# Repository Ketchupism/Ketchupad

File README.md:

# Ketchupad

A macropad with 4x3 11 switches, 1 rotary switch encoder
- This macropad will be frequently used paired with my macbook so I can use shortcuts in Fusion360, Kicad, opening tabs in chrome, and other software apps / tools
- The rotary Encoder is used for changing the LED's RGB colors
- The bottom case has a 15 degree tilt forward for visuals and less wrist movement
- Black, Red, and White are colors used in this design
- The 3D print includes the knob, top case, and bottom case. 

Challenges
- The worst part of this work was the firmware. The tutorial was hard to follow and a portion of making the QMK was vibecoded
- Making the case also took long because I added many details to be more unqiue and less boxy 

Features
- 11 keys with LED
- Rotary Encoder
- Custom knob for rotary encoder
- Custom case for PCB
- Angled macropad

Tools / Softwares / Resources
resources that are necessary to make this hackpad
- KiCad
- GrabCad
- Hack Club
- Fusion360
- 3D Printer 
- Soldering machine 

BOM
resources that are necessary to make this hackpad
- 1x PCB
- 1x Seeed XIAO RP2040 Microcontroller
- 11x Cherry MX Switches
- 1x EC11 Encoder with switch
- 11x white blank DSA keycaps
- 1x 3D printed case
- 11x through-hole 1N4148 diodes
- 11x SK6812 MINI-E LEDs
- 4x M3x16mm screws
- 4x M3x5mx4mm heatset inserts

Schematic Model

PCB Model

3D Viewing PCB Model

CAD Case Model + PCB Model 

Extra
- This macropad was inspired and funded by the Hack Club Hackpad Program
- This took way too long
- Currently, this project inspired me to move on to creating an entire custom keyboard, with repository https://github.com/Ketchupism/ketchboard , or in my profile to check out the progress i've done.

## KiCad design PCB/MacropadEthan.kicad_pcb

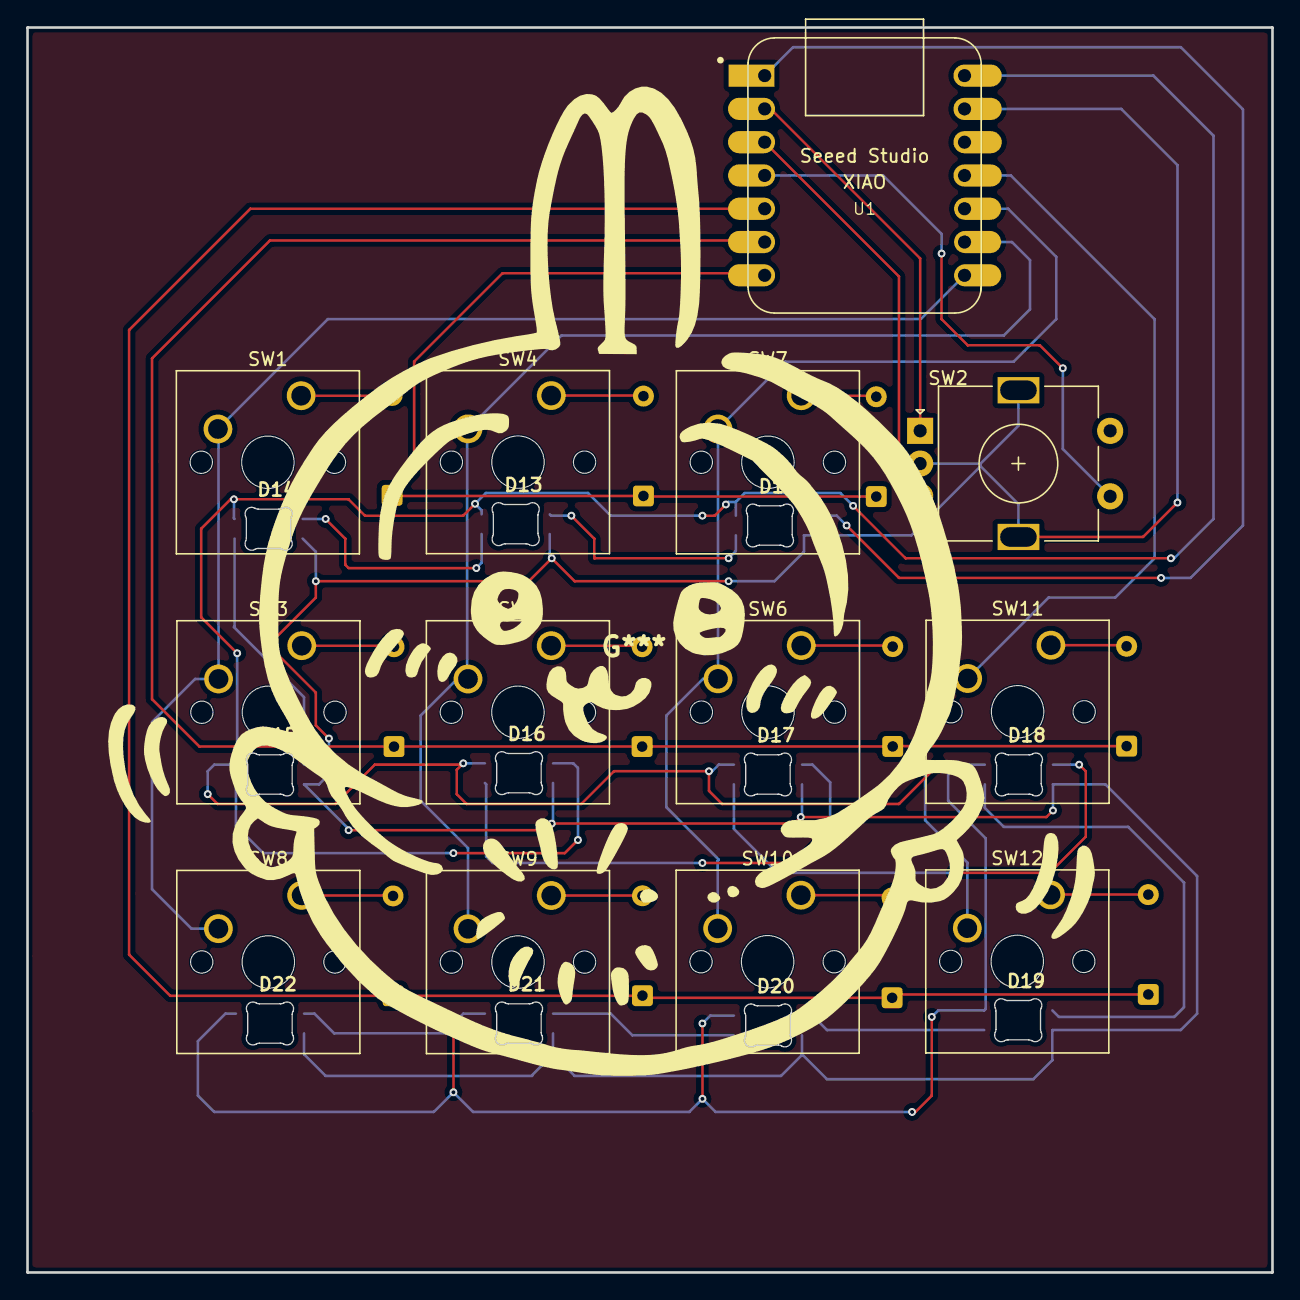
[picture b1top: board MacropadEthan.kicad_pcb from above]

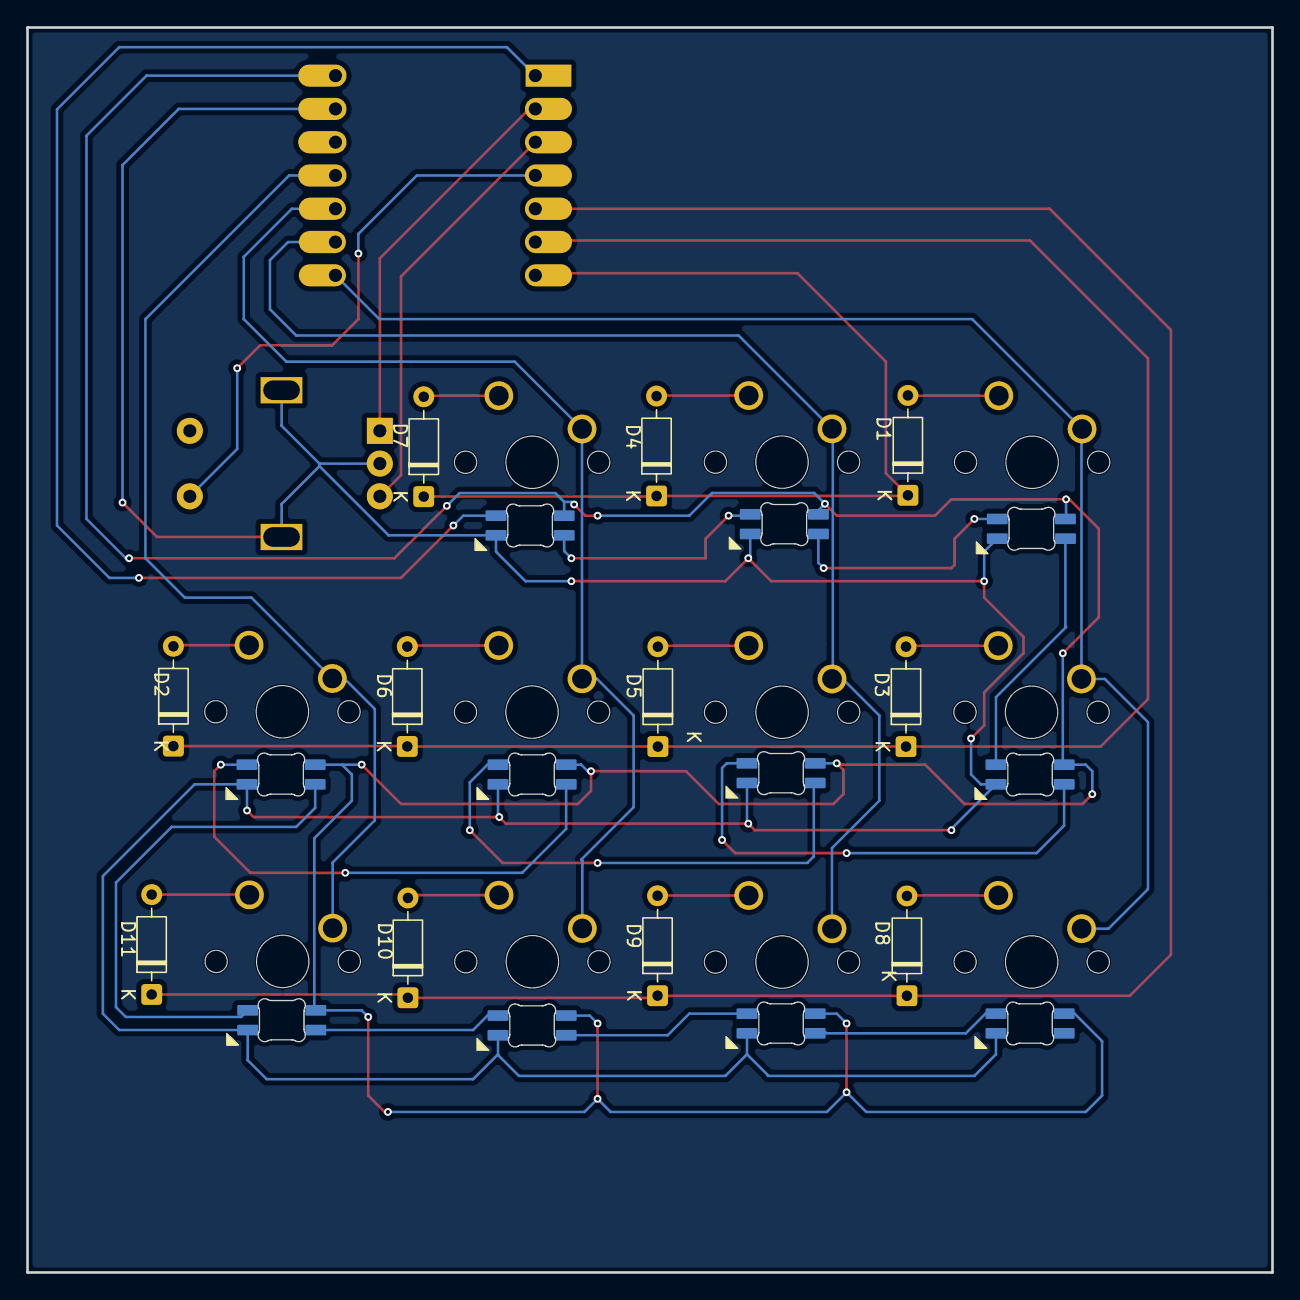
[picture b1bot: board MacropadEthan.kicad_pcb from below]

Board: 2 copper layers, 95.0 x 95.0 mm, 35 parts (11 on the bottom side), 34 nets.

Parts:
D1, D2, D3, D4, D5, D6, D7, D8, D9, D10, D11: 1N4148; D_DO-35_SOD27_P7.62mm_Horizontal
D12, D13, D14, D15, D16, D17, D18, D19, D20, D21, D22: SK6812MINI-E; SK6812MINI-E_fixed
SW1, SW3, SW4, SW5, SW6, SW7, SW8, SW9, SW10, SW11, SW12: SW_Push; SW_Cherry_MX_1.00u_PCB
SW2: RotaryEncoder_Switch; RotaryEncoder_Alps_EC11E-Switch_Vertical_H20mm
U1: MOUDLE-SEEEDUINO-XIAO; XIAO-Generic-Hybrid-14P-2.54-21X17.8MM

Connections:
+5V: D12.1 (VDD), D13.1 (VDD), D14.1 (VDD), D15.1 (VDD), D16.1 (VDD), D17.1 (VDD), D18.1 (VDD), D19.1 (VDD), D20.1 (VDD), D21.1 (VDD), D22.1 (VDD), U1.14 (5V)
Column 0: SW1.2, SW3.2, SW8.2, U1.8 (PB09_A7_D7_RX)
Column 1: SW4.2, SW5.2, SW9.2, U1.9 (PA7_A8_D8_SCK)
Column 2: SW6.2, SW7.2, SW10.2, U1.10 (PA5_A9_D9_MISO)
Column 3: SW11.2, SW12.2, U1.11 (PA6_A10_D10_MOSI)
EC11A: SW2.A, U1.2 (PA4_A1_D1)
EC11B: SW2.B, U1.3 (PA10_A2_D2)
EC11SWA: SW2.S1, U1.4 (PA11_A3_D3)
GND: D12.3 (VSS), D13.3 (VSS), D14.3 (VSS), D15.3 (VSS), D16.3 (VSS), D17.3 (VSS), D18.3 (VSS), D19.3 (VSS), D20.3 (VSS), D21.3 (VSS), D22.3 (VSS), SW2.C, SW2.MP, U1.13 (GND)
LED: D12.4 (DIN), U1.1 (PA02_A0_D0)
unnamed: D1.2 (A), SW1.1
unnamed: D2.2 (A), SW11.1
unnamed: D3.2 (A), SW3.1
unnamed: D4.2 (A), SW4.1
unnamed: D5.2 (A), SW5.1
unnamed: D6.2 (A), SW6.1
unnamed: D7.2 (A), SW7.1
unnamed: D8.2 (A), SW8.1
unnamed: D9.2 (A), SW9.1
unnamed: D10.2 (A), SW10.1
unnamed: D11.2 (A), SW12.1
unnamed: D12.2 (DOUT), D13.4 (DIN)
unnamed: D13.2 (DOUT), D14.4 (DIN)
unnamed: D14.2 (DOUT), D15.4 (DIN)
unnamed: D15.2 (DOUT), D16.4 (DIN)
unnamed: D16.2 (DOUT), D17.4 (DIN)
unnamed: D17.2 (DOUT), D18.4 (DIN)
unnamed: D18.2 (DOUT), D19.4 (DIN)
unnamed: D19.2 (DOUT), D20.4 (DIN)
unnamed: D20.2 (DOUT), D21.4 (DIN)
unnamed: D21.2 (DOUT), D22.4 (DIN)
Row 0: D8.1 (K), D9.1 (K), D10.1 (K), D11.1 (K), U1.5 (PA8_A4_D4_SDA)
Row 1: D2.1 (K), D3.1 (K), D5.1 (K), D6.1 (K), U1.6 (PA9_A5_D5_SCL)
Row 2: D1.1 (K), D4.1 (K), D7.1 (K), U1.7 (PB08_A6_D6_TX)
